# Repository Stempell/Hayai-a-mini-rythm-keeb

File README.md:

Hayai is a Mini keyboard for shortcuts and playing rythm games. It features 4 magnetic hall effect switches (each with an rgb underglow LED) a rotary encoder and an 0.96" IPS display.
The display is connected by a FPC cable to a ZIF socket. custom footprints are in the kicad files.
The whole thing runs on a rp2040.

Here's how it looks:

Hayai is desing around the Gateron magnetic jade air he dimensions but you can really use any magnetic switch you want, thanks to it's easy hotswap 

## Schematic

## PCB

dimensions of the pcb(and the acrylic plates) are roughly 84,5 x 48,7mm.

## Casing method
I took inspiration from the sayo device with the casing method with the pcb being sandwitched between the plates. I decided on a system where 4 holes will be occupied by screws attached from both sides to a female to female spacer, and the other 2 by dowel pins to prevent the plates from wobbling sideways.

The pcb sits inbetween the two middle plates with cutouts for components and pins

## Assembly
To assemble Hayai you'll need to follow these 4 simple steps:
1. Solder on all of the necesary components (you will have a bit less work to do if you choose pcba) The mcu can come with header pins pre-soldered on so you can make your job a bit easier for a like a dollar
2. Connect the display via the fpc cable with the panel facing upwards from the pcb and lay it flat on the board.
3. Sandwitch the pcb between the plates (look at the 3d model if you need some guidance) and put M3 dowel pins into the middle holes on the sides.
4. put M2 standoffs into the corner holes and screw them in with M2. this should hold the plates together. You can also add washers under the screws so it holds the plates better, M3 should fit.

Have fun! C:

## Bill of Materials

| # | Item | Quantity | Price | Link |
|---:|---|---:|---:|---|
| 1 | Custom PCB | 1 | ~$22.87 | [JLCPCB](https://jlcpcb.com/) |
| 2 | Acrylic plates | 4 | ~$18.04 | [Elecrow](https://www.elecrow.com/) |
| 3 | GATERON Magnetic Jade Air HE Switches | 4 | $15.00 | [GATERON](https://pl.aliexpress.com/item/1005005513800132.html?mp=1&pdp_npi=6%40dis%21PLN%21PLN+10.38%21PLN+5.19%21%21PLN+5.19%21%21%21%4021613be817913114503443671e1002%2112000033370341350%21ct%21PL%216850984236%21%211%210%21&gatewayAdapt=glo2pol) |
| 4 | Keycaps of choice | 4 | $1.34 | [AliExpress](https://pl.aliexpress.com/item/4000473863693.html) |
| 5 | 0.96" IPS TFT ST7735 display | 1 | $1.62 | [BuyDisplay](https://www.buydisplay.com/0-96-inch-mini-color-tft-lcd-display-module-80x160-ips-tft-st7735) |
| 6 | EC11 20mm switch rotary encoder with mounting plates (the cap i chose fits the one with a plum handle) | 1 | $1.38 | [AliExpress](https://pl.aliexpress.com/item/1005007644083514.html) |
| 7 | Encoder cap of choice | 1 | $3.24 | [AliExpress](https://pl.aliexpress.com/item/1005008583446552.html) |
| 8 | Waveshare RP2350-Zero Mini Development Board Female | 1 | $5.79 | [Waveshare](https://www.waveshare.com/rp2350-zero.htm) |
| 9 | 1x9 pin header for microcontroller | 2 | $2.45 | [AliExpress](https://tinyurl.com/3yzm8hka) |
| 10 | DRV5056A4QDBZR (SOT-23-3) | 4 | $3.36 | [JLCPCB](https://jlcpcb.com/partdetail/TexasInstruments-DRV5056A4QDBZR/C2152902) |
| 11 | Brass standoffs (M2, 13mm) | 4 | $3.28 | [AliExpress](https://pl.aliexpress.com/item/1005012002279754.html) |
| 12 | Dowel pins (M3, 14mm) | 4 | $4.11 | [AliExpress](https://pl.aliexpress.com/item/4000473863693.html) |
| 13 | M2 screws, can also add washers | 4 |  |  |
| 14 | SK6812-MINI-E LEDs | 4 | $2.01 | [AliExpress](https://pl.aliexpress.com/item/1005008308801366.html) |

Subtotal : $84.40

Note that the pcb and plates were made around these specific parts. You can experiment and switch them out for different models but i don't guarantee it'll work

## BIll of materials for the pcba assembly

| Designator | Comment | Footprint | JLCPCB Part # | Manufacturer | Lib Type | Qty | Price |
|---|---|---|---|---|---|---|---|
| C17 | 10uF | 0402 | [C15525](https://jlcpcb.com/partdetail/16204-CL05A106MQ5NUNC/C15525)| Samsung Electro-Mechanics | Basic | 2 | $0.0512 |
| C18,C19,C20,C21,C22,C24,C25,C26,C27 | 0.1uF | 0402 | [C1525](https://jlcpcb.com/partdetail/1877-CL05B104KO5NNNC/C1525) | Samsung Electro-Mechanics | Basic | 18 | $0.0810 |
| R5 | 18Ω | 0402 | [C25084](https://jlcpcb.com/partdetail/25827-0402WGF180JTCE/C25084) | UNI-ROYAL (Uniroyal Elec) | Extended | 20 | $0.0480 |
| R7 | 10kΩ | 0402 | [C25744](https://jlcpcb.com/partdetail/26487-0402WGF1002TCE/C25744) | UNI-ROYAL (Uniroyal Elec) | Basic | 2 | $0.0068 |
| U4 | ZIF connector, 8-pin, 0.5mm | ZIF_connector8pin0,5mm | [C2856828](https://jlcpcb.com/partdetail/XUNPU-FPC_05FB8PH20/C2856828) | XUNPU | Extended | 2 | $0.3208 |
|

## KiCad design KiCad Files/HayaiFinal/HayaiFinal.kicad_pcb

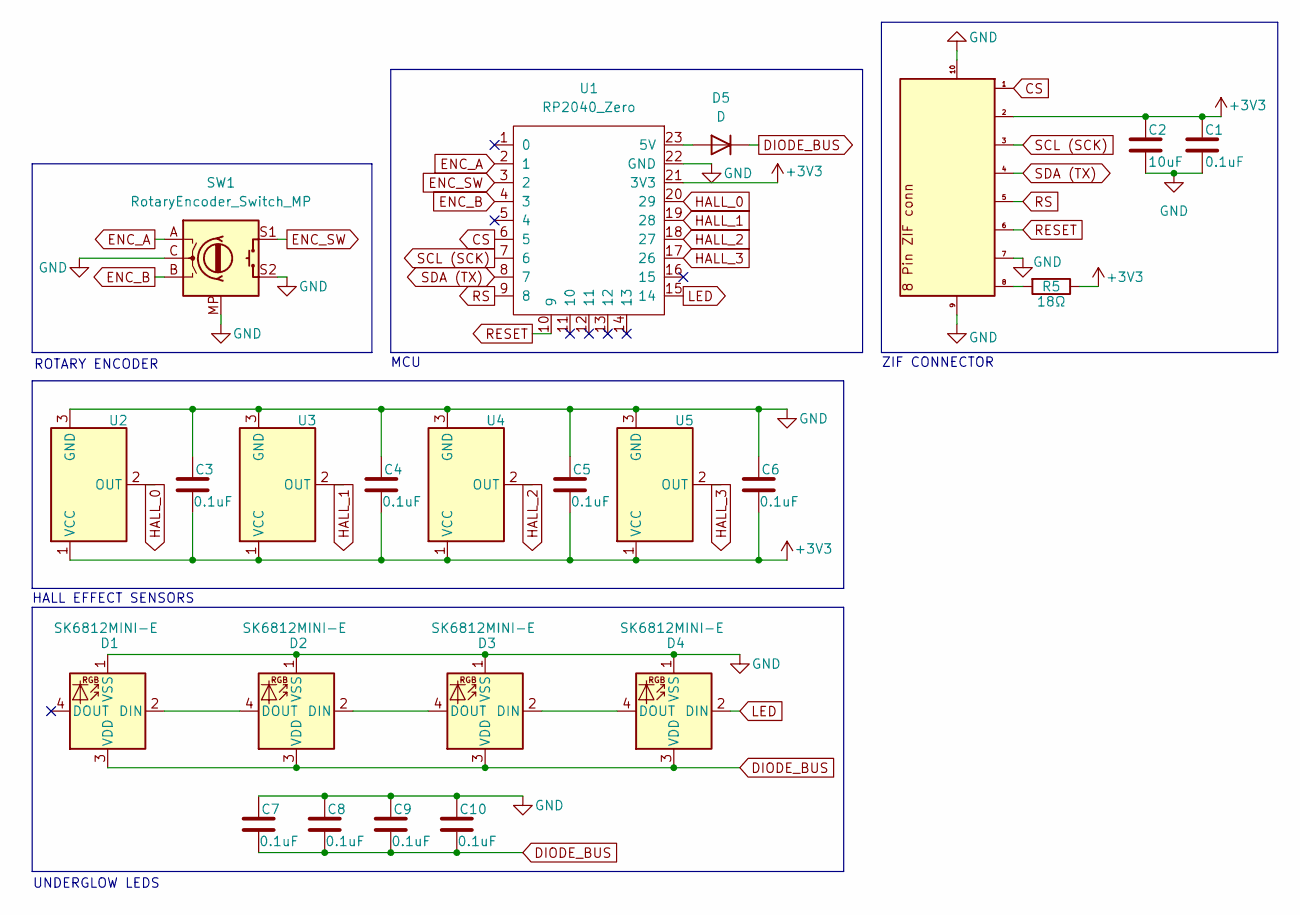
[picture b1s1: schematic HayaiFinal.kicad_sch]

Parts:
C1, C3, C4, C5, C6, C7, C8, C9, C10: 0.1uF; C_0402_1005Metric
C2: 10uF; C_0603_1608Metric
D1, D2, D3, D4: SK6812MINI-E; LED_SK6812MINI-E_3.2x2.8mm_P1.5mm_ReverseMount
D5: D; Diode_DO-35
R5: 18Ω; R_0402_1005Metric
SW1: RotaryEncoder_Switch_MP; RotaryEncoder_Alps_EC11E-Switch_Vertical_H20mm_MountingHoles
U1: RP2040_Zero
U2, U3, U4, U5: DRV5055A4xDBZxQ1; SOT-23
U6: ZIF_connector 8 pin 0,5mm

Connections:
+3V3: C1.1, C2.1, C3.2, C4.2, C5.2, C6.2, R5.1, U1.21 (3V3), U2.1 (VCC), U3.1 (VCC), U4.1 (VCC), U5.1 (VCC), U6.2
CS: U1.6 (5), U6.1
DIODE_BUS: C7.2, C8.2, C9.2, C10.2, D1.3 (VDD), D2.3 (VDD), D3.3 (VDD), D4.3 (VDD), D5.1 (K)
ENC_A: SW1.A, U1.2 (1)
ENC_B: SW1.B, U1.4 (3)
ENC_SW: SW1.S1, U1.3 (2)
GND: C1.2, C2.2, C3.1, C4.1, C5.1, C6.1, C7.1, C8.1, C9.1, C10.1, D1.1 (VSS), D2.1 (VSS), D3.1 (VSS), D4.1 (VSS), SW1.C, SW1.MP, SW1.S2, U1.22 (GND), U2.3 (GND), U3.3 (GND), U4.3 (GND), U5.3 (GND), U6.7, U6.9, U6.10
HALL_0: U1.20 (29), U2.2 (OUT)
HALL_1: U1.19 (28), U3.2 (OUT)
HALL_2: U1.18 (27), U4.2 (OUT)
HALL_3: U1.17 (26), U5.2 (OUT)
LED: D4.2 (DIN), U1.15 (14)
unnamed: D1.2 (DIN), D2.4 (DOUT)
unnamed: D2.2 (DIN), D3.4 (DOUT)
unnamed: D3.2 (DIN), D4.4 (DOUT)
unnamed: D5.2 (A), U1.23 (5V)
unnamed: R5.2, U6.8
RESET: U1.10 (9), U6.6
RS: U1.9 (8), U6.5
SCL (SCK): U1.7 (6), U6.3
SDA (TX): U1.8 (7), U6.4

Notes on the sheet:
HALL EFFECT SENSORS
ROTARY ENCODER
UNDERGLOW LEDS
ZIF CONNECTOR
MCU

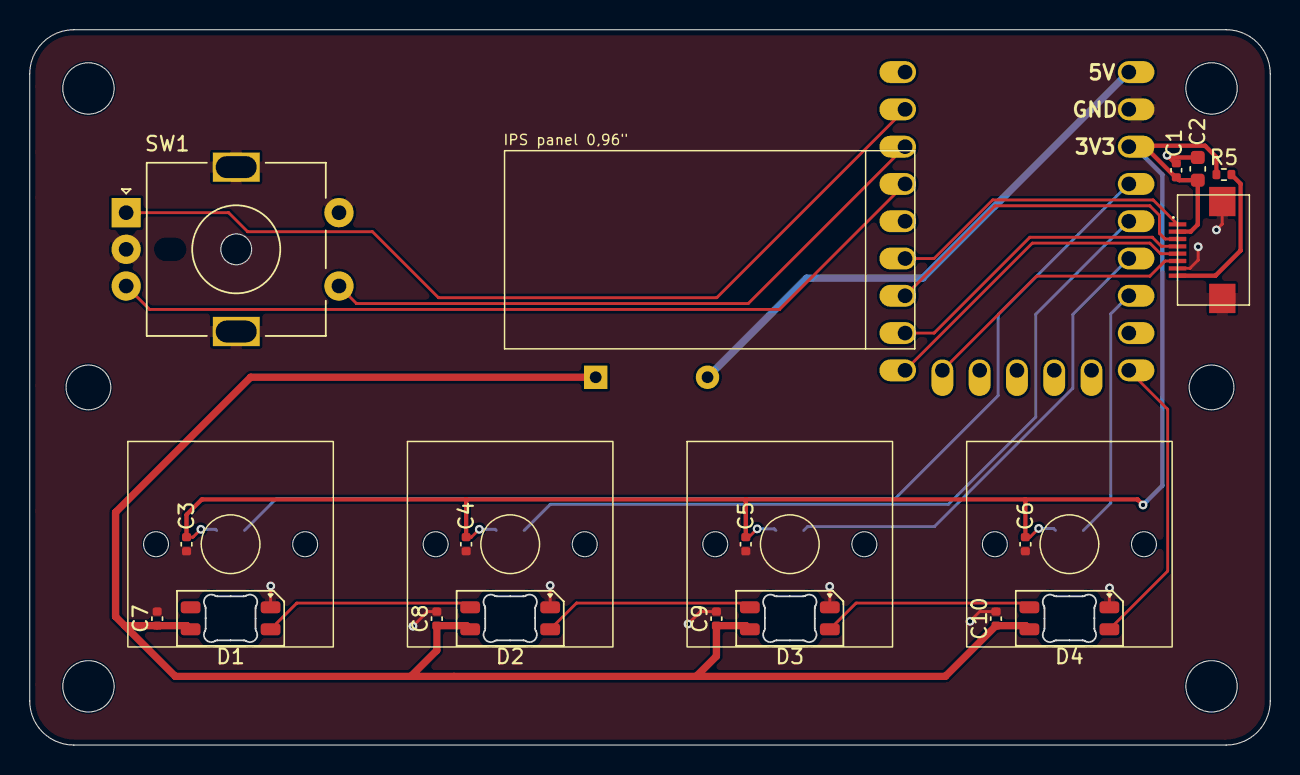
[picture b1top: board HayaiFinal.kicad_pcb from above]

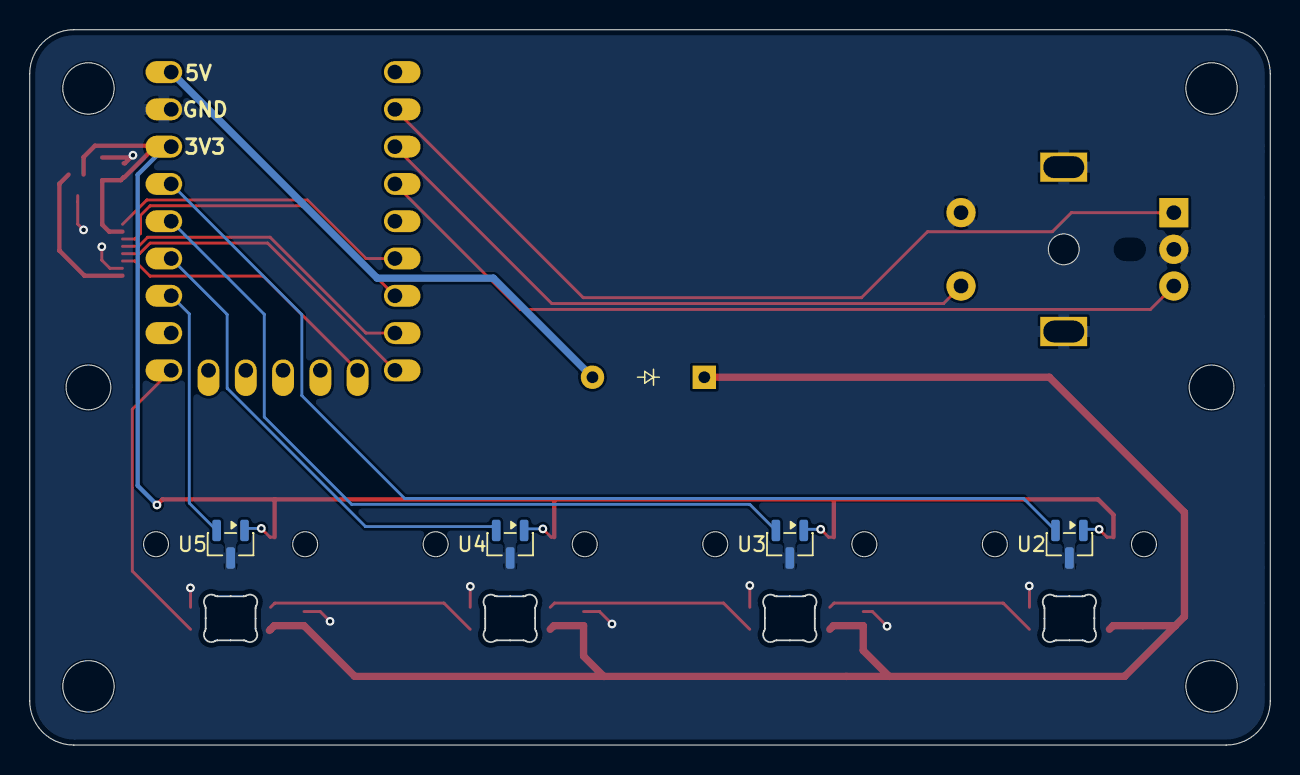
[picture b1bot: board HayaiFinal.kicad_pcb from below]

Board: 2 copper layers, 84.5 x 48.7 mm, 23 parts (6 on the bottom side), 21 nets.

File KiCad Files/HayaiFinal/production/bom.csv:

Designator,Footprint,Quantity,Value,LCSC Part #
"C1, C10, C3, C4, C5, C6, C7, C8, C9",0402,9,0.1uF,
C2,0603,1,10uF,
"D1, D2, D3, D4",LED_SK6812MINI-E_3.2x2.8mm_P1.5mm_ReverseMount,4,SK6812MINI-E,
D5,Diode_DO-35,1,D,
R5,0402,1,18Ω,
SW1,RotaryEncoder_Alps_EC11E-Switch_Vertical_H20mm_MountingHoles,1,RotaryEncoder_Switch_MP,
U1,RP2040_Zero,1,RP2040_Zero,
"U2, U3, U4, U5",SOT-23,4,DRV5055A4xDBZxQ1,
U6,"ZIF_connector 8 pin 0,5mm",1,~,

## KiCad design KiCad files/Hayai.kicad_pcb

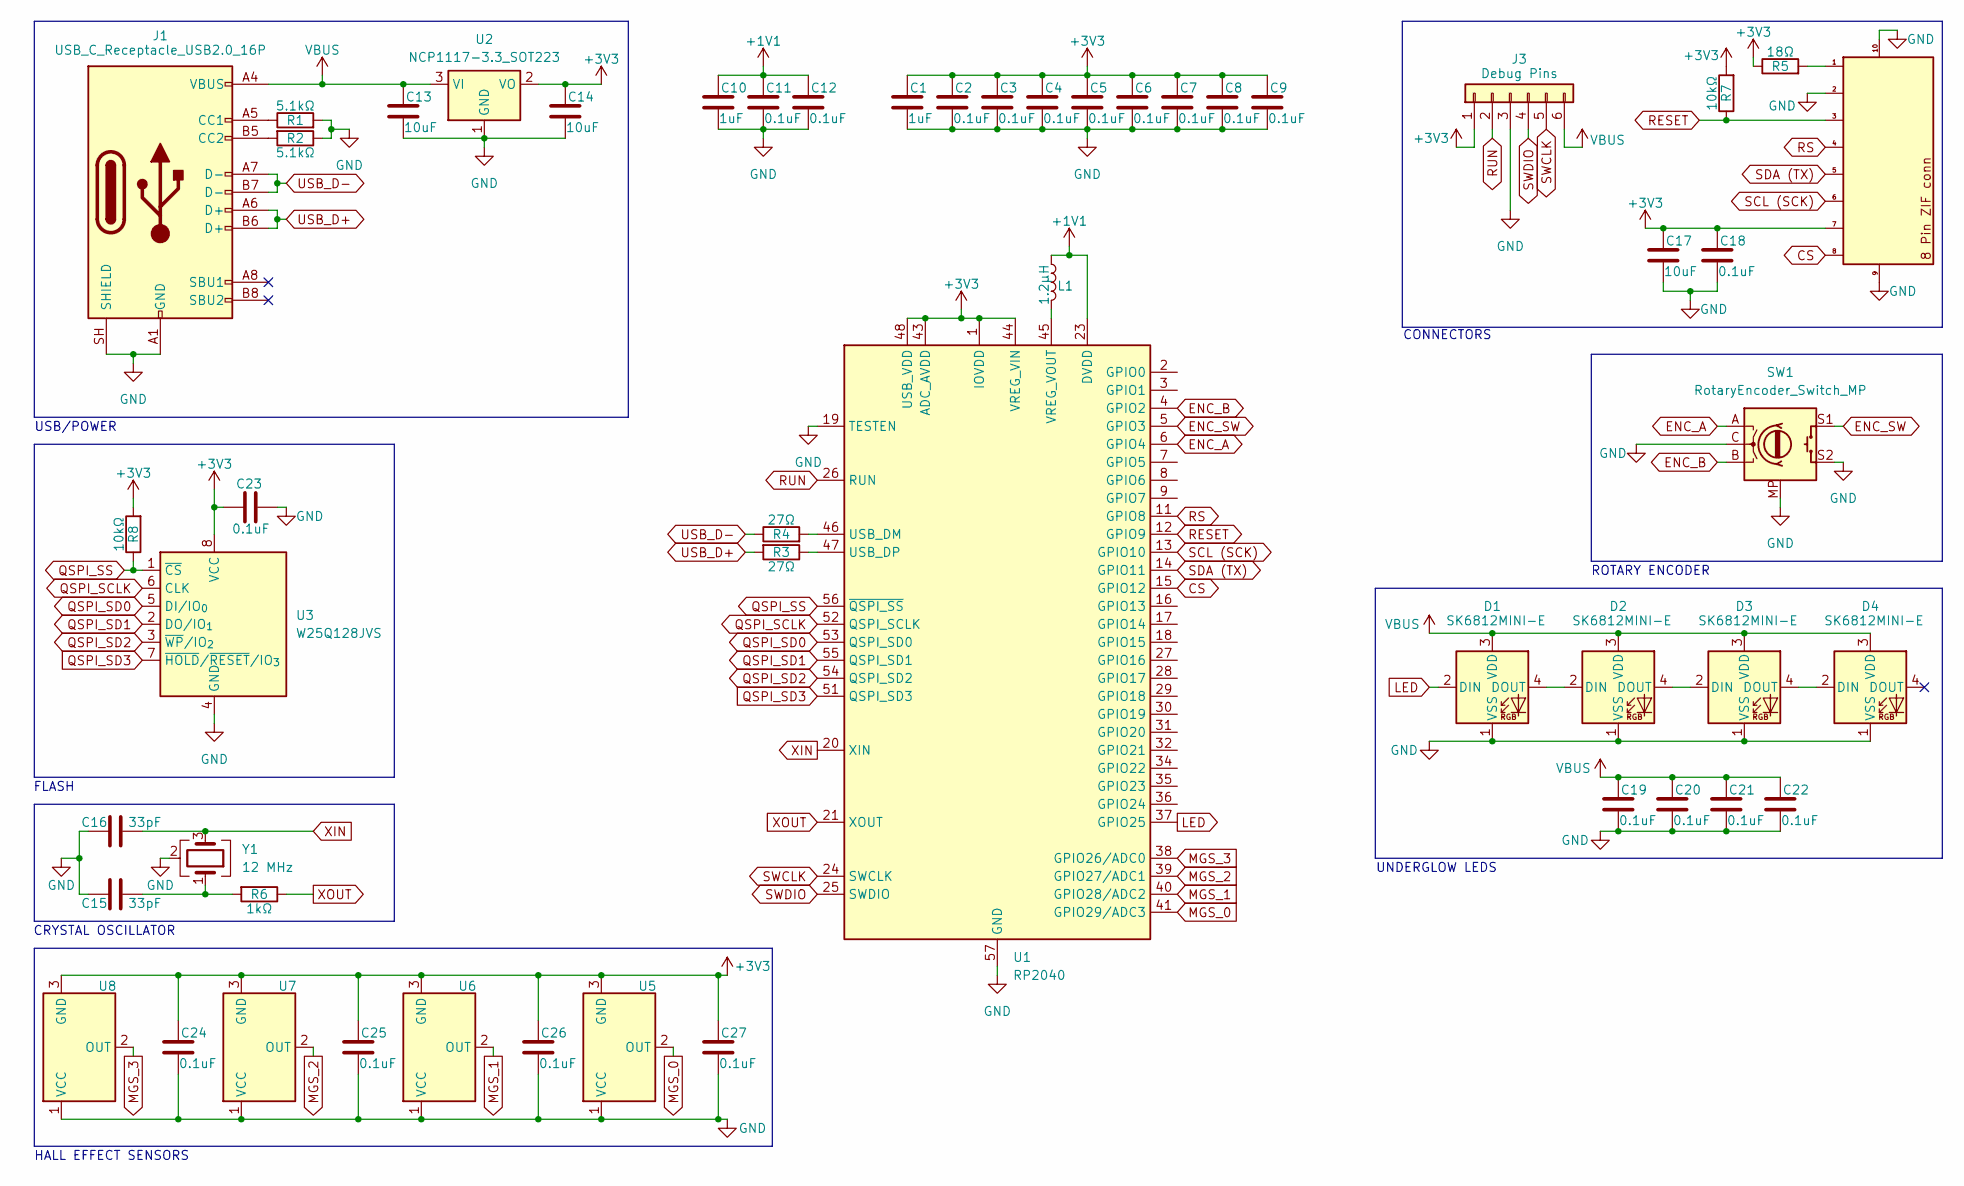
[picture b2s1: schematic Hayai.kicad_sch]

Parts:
C1, C10: 1uF; C_0402_1005Metric
C2, C3, C4, C5, C6, C7, C8, C9, C11, C12, C18, C19, C20, C21, C22, C23, C24, C25, C26, C27: 0.1uF; C_0402_1005Metric
C13, C14: 10uF; C_0603_1608Metric
C15, C16: 33pF; C_0402_1005Metric
C17: 10uF; C_0402_1005Metric
D1, D2, D3, D4: SK6812MINI-E; LED_SK6812MINI-E_3.2x2.8mm_P1.5mm_ReverseMount
J1: USB_C_Receptacle_USB2.0_16P; USB_C_HRO_TYPE-C-31-M-12
J3: Debug Pins; PinHeader_1x06_P2.54mm_Vertical
L1: 1.2µH; L_0402_1005Metric
R1, R2: 5.1kΩ; R_0402_1005Metric
R3, R4: 27Ω; R_0402_1005Metric
R5: 18Ω; R_0402_1005Metric
R6: 1kΩ; R_0402_1005Metric
R7, R8: 10kΩ; R_0402_1005Metric
SW1: RotaryEncoder_Switch_MP; RotaryEncoder_Alps_EC11E-Switch_Vertical_H20mm_MountingHoles
U1: RP2040; QFN-56-1EP_7x7mm_P0.4mm_EP3.2x3.2mm
U2: NCP1117-3.3_SOT223; SOT-23-3
U3: W25Q128JVS; SOIC-8_5.3x5.3mm_P1.27mm
U4: ZIF_connector 8 pin 0,5mm
U5, U6, U7, U8: DRV5055A4xDBZxQ1; SOT-23
Y1: 12 MHz; Crystal_SMD_3225-4Pin_3.2x2.5mm

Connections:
+1V1: C10.1, C11.1, C12.1, L1.1, U1.23 (DVDD), U1.50 (DVDD)
+3V3: C1.1, C2.1, C3.1, C4.1, C5.1, C6.1, C7.1, C8.1, C9.1, C14.1, C17.1, C18.1, C23.1, C24.1, C25.1, C26.1, C27.1, J3.1, R5.1, R7.2, R8.2, U1.1 (IOVDD), U1.10 (IOVDD), U1.22 (IOVDD), U1.33 (IOVDD), U1.42 (IOVDD), U1.43 (ADC_AVDD), U1.44 (VREG_VIN), U1.48 (USB_VDD), U1.49 (IOVDD), U2.2 (VO), U3.8 (VCC), U4.7, U5.3 (GND), U6.3 (GND), U7.3 (GND), U8.3 (GND)
CS: U1.15 (GPIO12), U4.8
ENC_A: SW1.A, U1.6 (GPIO4)
ENC_B: SW1.B, U1.4 (GPIO2)
ENC_SW: SW1.S1, U1.5 (GPIO3)
GND: C1.2, C2.2, C3.2, C4.2, C5.2, C6.2, C7.2, C8.2, C9.2, C10.2, C11.2, C12.2, C13.2, C14.2, C15.1, C16.1, C17.2, C18.2, C19.2, C20.2, C21.2, C22.2, C23.2, C24.2, C25.2, C26.2, C27.2, D1.1 (VSS), D2.1 (VSS), D3.1 (VSS), D4.1 (VSS), J1.A1 (GND), J1.A12 (GND), J1.B1 (GND), J1.B12 (GND), J1.SH (SHIELD), J3.3, R1.2, R2.1, SW1.C, SW1.MP, SW1.S2, U1.19 (TESTEN), U1.57 (GND), U2.1 (GND), U3.4 (GND), U4.2, U4.9, U4.10, U5.1 (VCC), U6.1 (VCC), U7.1 (VCC), U8.1 (VCC), Y1.2 (G), Y1.4 (G)
LED: D1.2 (DIN), U1.37 (GPIO25)
MGS_0: U1.41 (GPIO29/ADC3), U5.2 (OUT)
MGS_1: U1.40 (GPIO28/ADC2), U6.2 (OUT)
MGS_2: U1.39 (GPIO27/ADC1), U7.2 (OUT)
MGS_3: U1.38 (GPIO26/ADC0), U8.2 (OUT)
unnamed: C15.2, R6.2, Y1.1
unnamed: D1.4 (DOUT), D2.2 (DIN)
unnamed: D2.4 (DOUT), D3.2 (DIN)
unnamed: D3.4 (DOUT), D4.2 (DIN)
unnamed: J1.A5 (CC1), R1.1
unnamed: J1.B5 (CC2), R2.2
unnamed: R5.2, U4.1
unnamed: R4.2, U1.46 (USB_DM)
unnamed: R3.1, U1.47 (USB_DP)
unnamed: L1.2, U1.45 (VREG_VOUT)
QSPI_SCLK: U1.52 (QSPI_SCLK), U3.6 (CLK)
QSPI_SD0: U1.53 (QSPI_SD0), U3.5 (DI/IO_{0})
QSPI_SD1: U1.55 (QSPI_SD1), U3.2 (DO/IO_{1})
QSPI_SD2: U1.54 (QSPI_SD2), U3.3 (~WP/IO_{2})
QSPI_SD3: U1.51 (QSPI_SD3), U3.7 (~HOLD/~RESET/IO_{3})
QSPI_SS: R8.1, U1.56 (~QSPI_SS), U3.1 (~CS)
RESET: R7.1, U1.12 (GPIO9), U4.3
RS: U1.11 (GPIO8), U4.4
RUN: J3.2, U1.26 (RUN)
SCL (SCK): U1.13 (GPIO10), U4.6
SDA (TX): U1.14 (GPIO11), U4.5
SWCLK: J3.5, U1.24 (SWCLK)
SWDIO: J3.4, U1.25 (SWDIO)
USB_D+: J1.A6 (D+), J1.B6 (D+), R3.2
USB_D-: J1.A7 (D-), J1.B7 (D-), R4.1
VBUS: C13.1, C19.1, C20.1, C21.1, C22.1, D1.3 (VDD), D2.3 (VDD), D3.3 (VDD), D4.3 (VDD), J1.A4 (VBUS), J1.A9 (VBUS), J1.B4 (VBUS), J1.B9 (VBUS), J3.6, U2.3 (VI)
XIN: C16.2, U1.20 (XIN), Y1.3
XOUT: R6.1, U1.21 (XOUT)

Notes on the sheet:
FLASH
ROTARY ENCODER
USB/POWER
UNDERGLOW LEDS
CRYSTAL OSCILLATOR
HALL EFFECT SENSORS
CONNECTORS

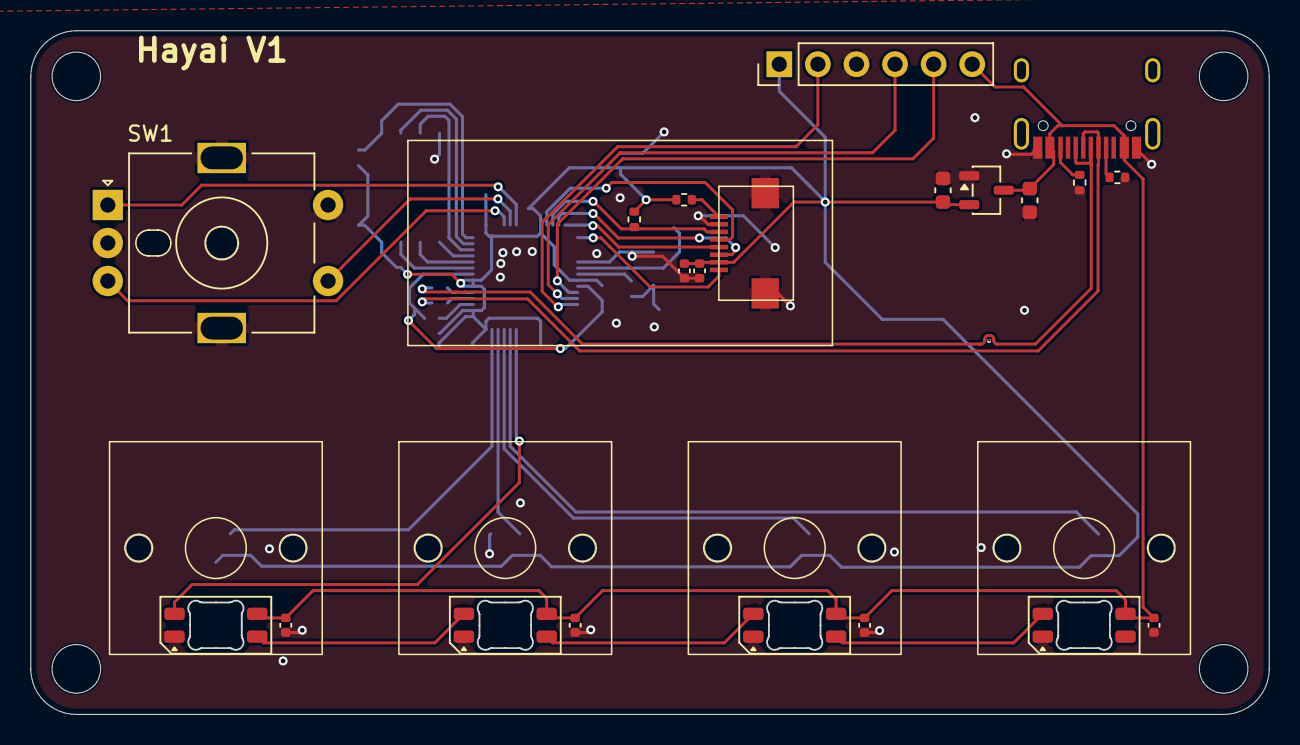
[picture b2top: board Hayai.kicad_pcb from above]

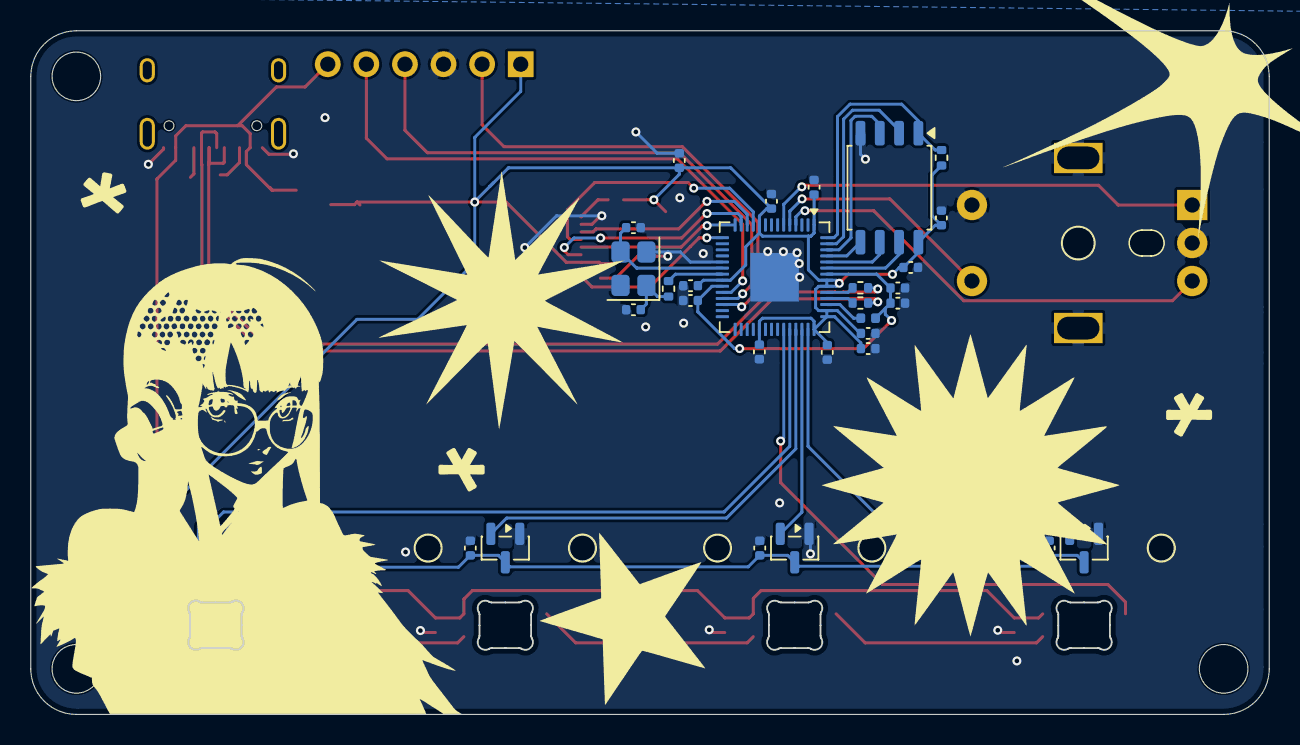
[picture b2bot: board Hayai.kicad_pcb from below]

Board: 2 copper layers, 81.5 x 45.0 mm, 52 parts (31 on the bottom side), 40 nets.

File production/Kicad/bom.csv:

Designator,Footprint,Quantity,Value,LCSC Part #
"C1, C10",0402,2,1uF,
"C11, C12, C18, C19, C2, C20, C21, C22, C23, C24, C25, C26, C27, C3, C4, C5, C6, C7, C8, C9",0402,20,0.1uF,
"C13, C14",0603,2,10uF,
"C15, C16",0402,2,33pF,
C17,0402,1,10uF,
"D1, D2, D3, D4",LED_SK6812MINI-E_3.2x2.8mm_P1.5mm_ReverseMount,4,SK6812MINI-E,
J1,USB_C_HRO_TYPE-C-31-M-12,1,USB_C_Receptacle_USB2.0_16P,
J3,PinHeader_1x06_P2.54mm_Vertical,1,Debug Pins,
L1,0402,1,1.2µH,
"R1, R2",0402,2,5.1kΩ,
"R3, R4",0402,2,27Ω,
R5,0402,1,18Ω,
R6,0402,1,1kΩ,
"R7, R8",0402,2,10kΩ,
SW1,RotaryEncoder_Alps_EC11E-Switch_Vertical_H20mm_MountingHoles,1,RotaryEncoder_Switch_MP,
U1,QFN-56-1EP_7x7mm_P0.4mm_EP3.2x3.2mm,1,RP2040,
U2,SOT-23-3,1,NCP1117-3.3_SOT223,
U3,SOIC-8_5.3x5.3mm_P1.27mm,1,W25Q128JVS,
U4,"ZIF_connector 8 pin 0,5mm",1,~,
"U5, U6, U7, U8",SOT-23,4,DRV5055A4xDBZxQ1,
Y1,Crystal_SMD_3225-4Pin_3.2x2.5mm,1,12 MHz,
